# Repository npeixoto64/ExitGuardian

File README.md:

# ExitGuardian
A full product project that watches windows with wireless sensors and has a gateway for the main door with wireless sensors.
When the user opens the exit door to leave, it checks for open windows and doors.

# Documentation
## How to generate the documentation
$ python3 -m venv .venv
$ source .venv/bin/activate
$ pip install -r requirements.txt
$ make html

## Deactivate the python virtual environment
$ deactivate
$ rm -rf .venv

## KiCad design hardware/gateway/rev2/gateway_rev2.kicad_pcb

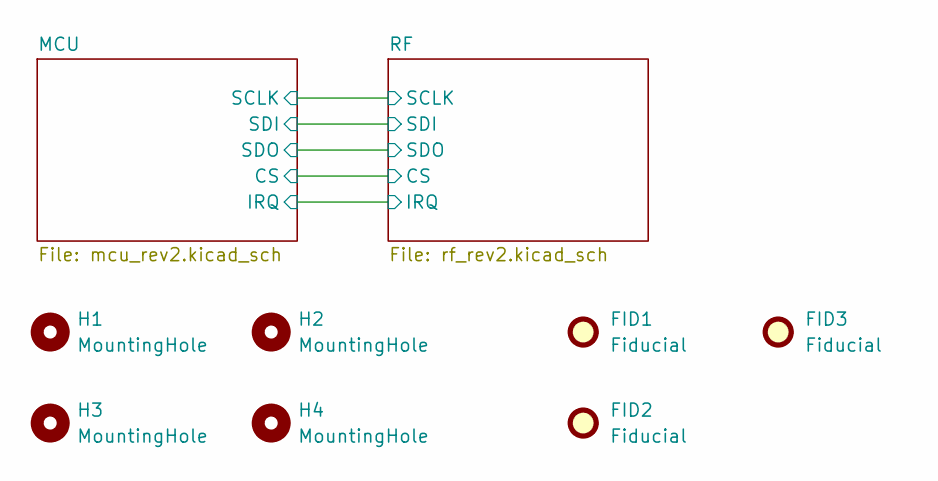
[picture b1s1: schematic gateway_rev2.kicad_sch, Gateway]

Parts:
FID1, FID2, FID3: Fiducial; Fiducial_1mm_Mask2mm
H1, H2, H3, H4: MountingHole; MountingHole_2.5mm

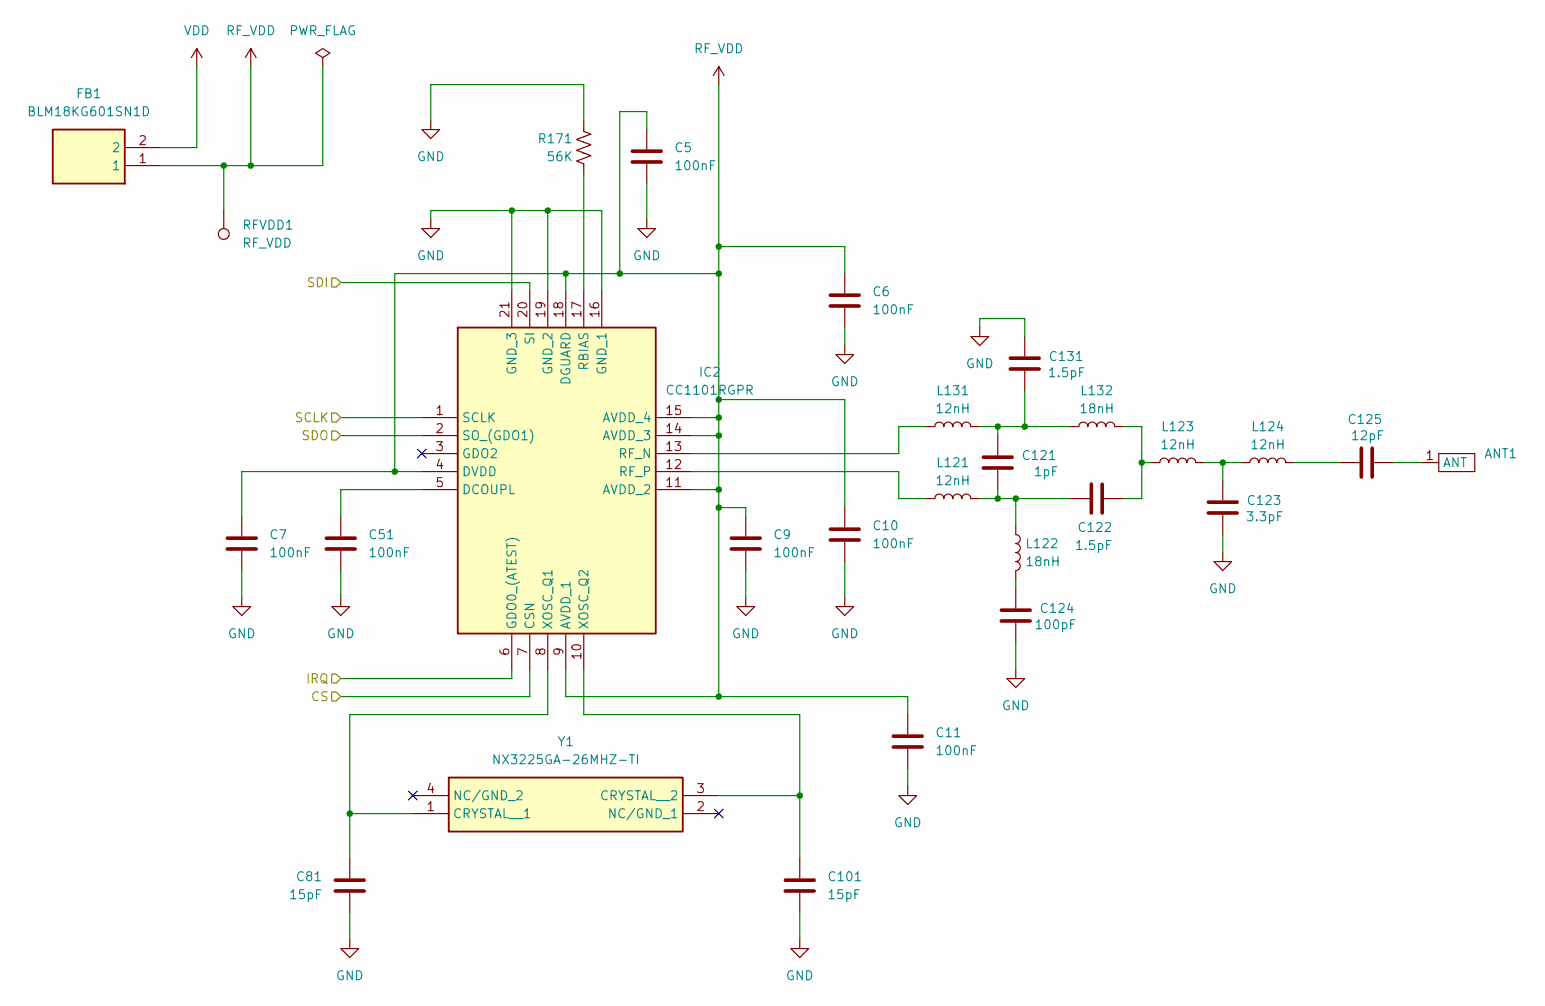
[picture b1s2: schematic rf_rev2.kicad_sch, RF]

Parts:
ANT1: Antenna_hole
C5, C6, C7, C9, C10, C11, C51: 100nF; C_0402_1005Metric; Mouser Part Number 603-CC402KRX7R7BB104
C81, C101: 15pF; C_0402_1005Metric; Mouser Part Number 77-VJ0402D150FXCAJ
C121: 1pF; C_0402_1005Metric; Mouser Part Number 81-GRM1555C1H1R0BA1J
C122, C131: 1.5pF; C_0402_1005Metric; Mouser Part Number 81-GRM1555C1E1R5BA1D
C123: 3.3pF; C_0402_1005Metric; Mouser Part Number 81-GRM1555C1H3R3WA1D
C124: 100pF; C_0402_1005Metric; Mouser Part Number 81-GRM1555C1H101FA1J
C125: 12pF; C_0402_1005Metric; Mouser Part Number 81-GRM1555C1H120FA1D
FB1: BLM18KG601SN1D; BLM18SP221SN1B; Mouser Part Number 81-BLM18KG601SN1D
IC2: CC1101RGPR; QFN50P400X400X100-21N-D; Mouser Part Number 595-CC1101RGPR
L121, L123, L124, L131: 12nH; L_0402_1005Metric; Mouser Part Number 81-LQW15AN12NJ80D
L122, L132: 18nH; L_0402_1005Metric; Mouser Part Number 81-LQG15HH18NJ02D
R171: 56K; R_0402_1005Metric; Mouser Part Number 667-ERJ-PA2F5602X
RFVDD1: RF_VDD; TestPoint_Pad_D1.0mm
Y1: NX3225GA-26MHZ-TI; NX3225GA26000MSTDCRG2; Mouser Part Number 344-NX3225GA26MHZTI

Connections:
/MCU/CS: IC2.7 (CSN); also elsewhere on the board
/MCU/IRQ: IC2.6 (GDO0_(ATEST)); also elsewhere on the board
/MCU/SCLK: IC2.1 (SCLK); also elsewhere on the board
/MCU/SDI: IC2.20 (SI); also elsewhere on the board
/MCU/SDO: IC2.2 (SO_(GDO1)); also elsewhere on the board
GND: C5.2, C6.2, C7.2, C9.2, C10.2, C11.2, C51.2, C81.2, C101.2, C123.1, C124.1, C131.2, IC2.16 (GND_1), IC2.19 (GND_2), IC2.21 (GND_3), R171.2; also elsewhere on the board
unnamed: ANT1.1 (ANT_1), C125.2
unnamed: C121.1, C122.1, L121.2, L122.1
unnamed: C121.2, C131.1, L131.2, L132.1
unnamed: C122.2, L123.1, L132.2
unnamed: C123.2, L123.2, L124.1
unnamed: C124.2, L122.2
unnamed: C125.1, L124.2
unnamed: C51.1, IC2.5 (DCOUPL)
unnamed: IC2.17 (RBIAS), R171.1
unnamed: IC2.13 (RF_N), L131.1
unnamed: IC2.12 (RF_P), L121.1
unnamed: C81.1, IC2.8 (XOSC_Q1), Y1.1 (CRYSTAL__1)
unnamed: C101.1, IC2.10 (XOSC_Q2), Y1.3 (CRYSTAL__2)
RF_VDD: C5.1, C6.1, C7.1, C9.1, C10.1, C11.1, FB1.1, IC2.4 (DVDD), IC2.9 (AVDD_1), IC2.11 (AVDD_2), IC2.14 (AVDD_3), IC2.15 (AVDD_4), IC2.18 (DGUARD), RFVDD1.1 (1_1)
VDD: FB1.2; also elsewhere on the board

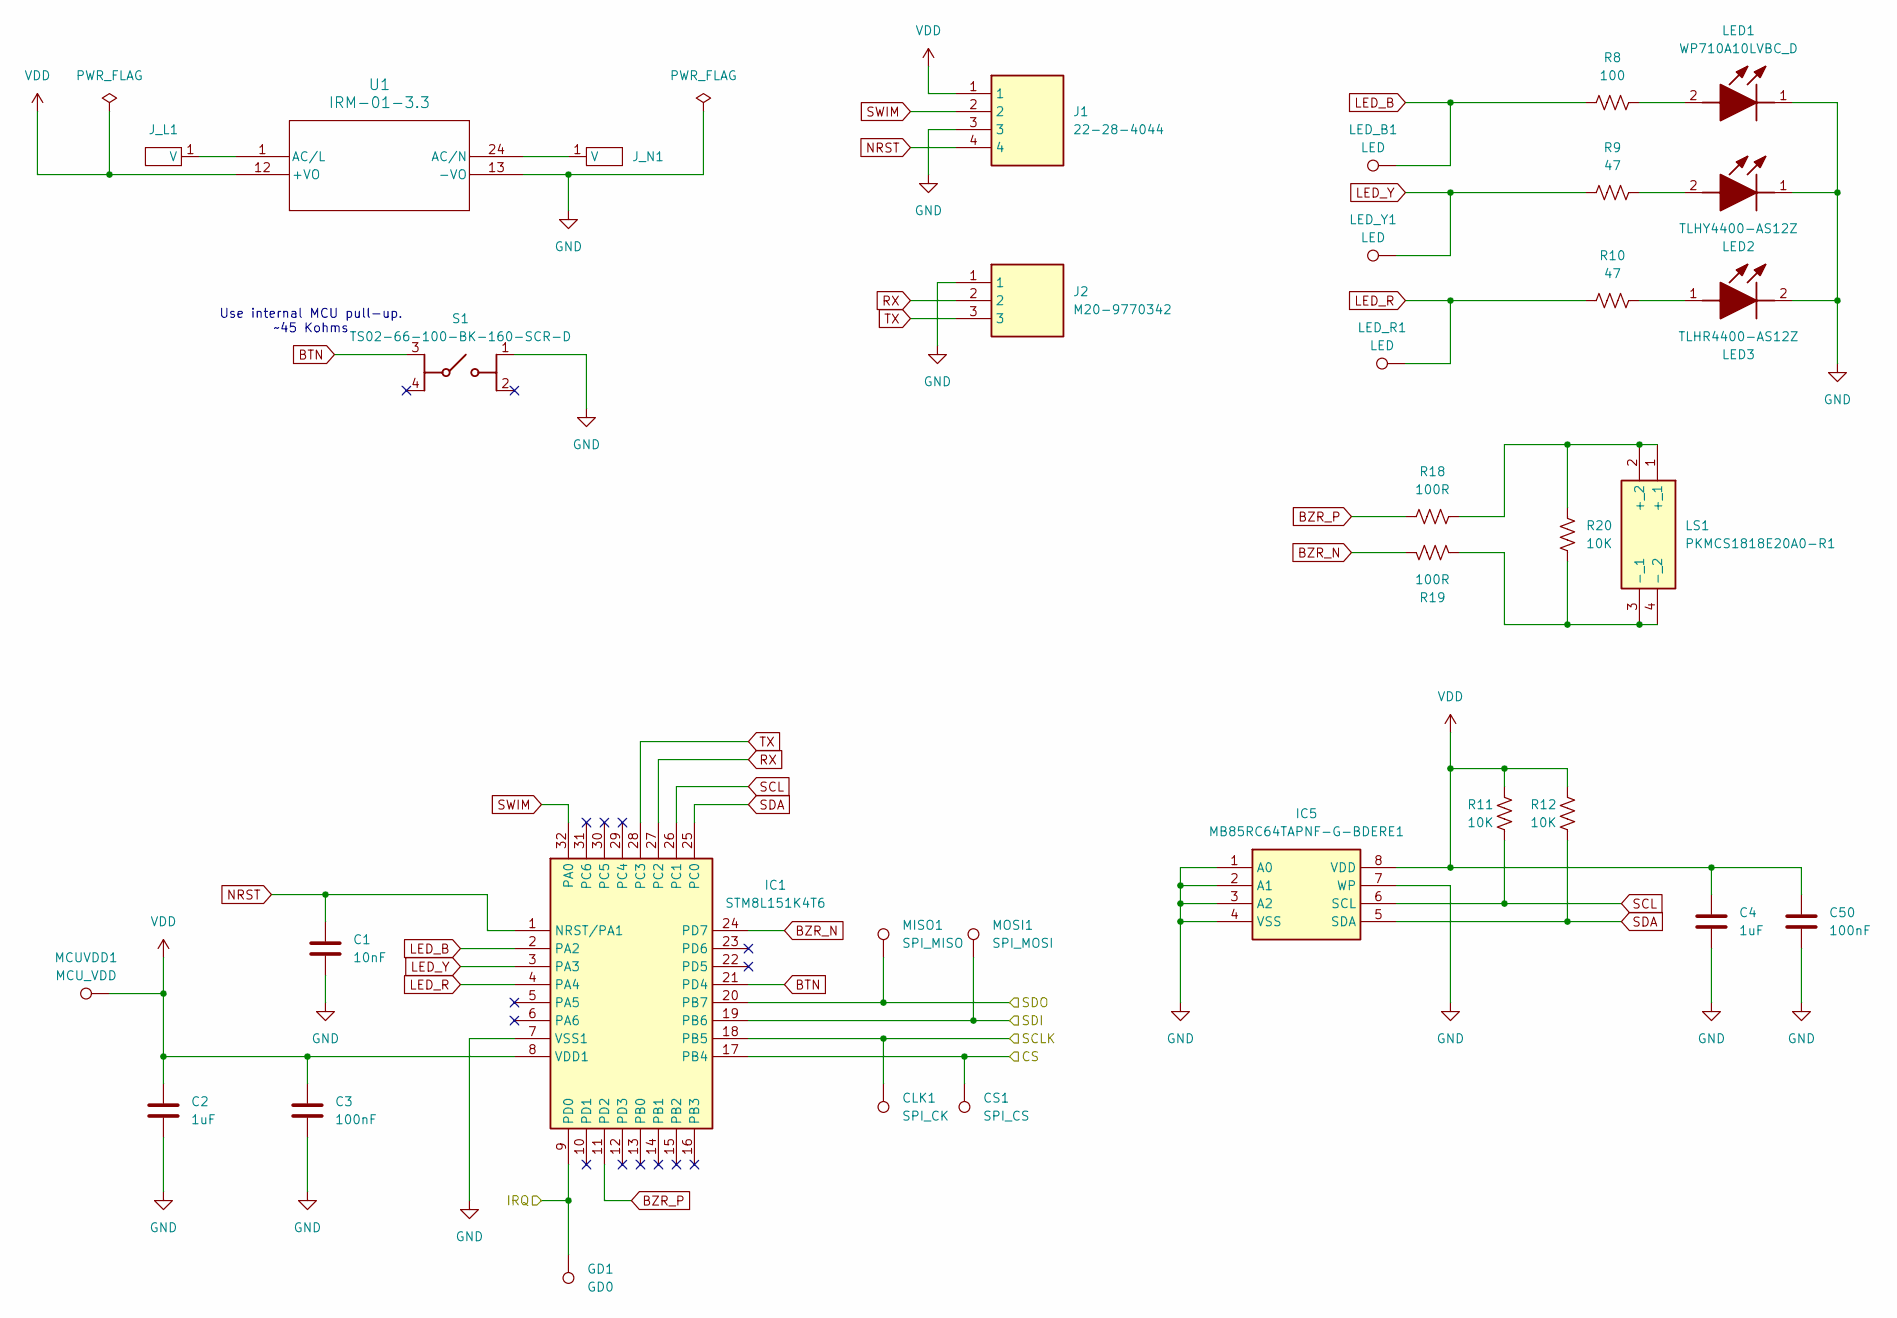
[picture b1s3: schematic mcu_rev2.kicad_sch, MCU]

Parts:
C1: 10nF; C_0402_1005Metric; Mouser Part Number 963-MSAST105SB7103KF
C2, C4: 1uF; C_0402_1005Metric; Mouser Part Number 581-KGM05AV50J105ZH
C3, C50: 100nF; C_0402_1005Metric; Mouser Part Number 603-CC402KRX7R7BB104
CLK1: SPI_CK; TestPoint_Pad_D1.0mm
CS1: SPI_CS; TestPoint_Pad_D1.0mm
GD1: GD0; TestPoint_Pad_D1.0mm
IC1: STM8L151K4T6; QFP80P900X900X160-32N; Mouser Part Number 511-STM8L151K4T6
IC5: MB85RC64TAPNF-G-BDERE1; SOIC127P602X173-8N; Mouser Part Number 249-85C64TAPNFGBDR1
J1: 22-28-4044; HDRV4W66P0X254_1X4_1016X249X1067P; Mouser Part Number 538-22-28-4044
J2: M20-9770342; HDRV3W66P0X254_1X3_762X254X855P; Mouser Part Number 855-M20-9770342
J_L1: 230V
J_N1: 230V
LED1: WP710A10LVBC_D; WP710A10LVBCD; Mouser Part Number 604-WP710A10LVBCD
LED2: TLHY4400-AS12Z; TLHY4400AS12Z; Mouser Part Number 78-TLHY4400-AS12Z
LED3: TLHR4400-AS12Z; TLHR4400AS12Z; Mouser Part Number 78-TLHY4400-AS12Z
LED_B1: LED; TestPoint_Pad_D1.0mm
LED_R1: LED; TestPoint_Pad_D1.0mm
LED_Y1: LED; TestPoint_Pad_D1.0mm
LS1: PKMCS1818E20A0-R1; PKMCS1818E20A0R1; Mouser Part Number 81-PKMCS1818E20A0-R1
MCUVDD1: MCU_VDD; TestPoint_Pad_D1.0mm
MISO1: SPI_MISO; TestPoint_Pad_D1.0mm
MOSI1: SPI_MOSI; TestPoint_Pad_D1.0mm
R8: 100; R_0402_1005Metric; Mouser Part Number 594-MCS04020C1000FE0
R9, R10: 47; R_0402_1005Metric; Mouser Part Number 594-MCS04020C4709FE0
R11, R12, R20: 10K; R_0402_1005Metric; Mouser Part Number 594-MCS04020C1002FE0
R18, R19: 100R; R_0402_1005Metric; Mouser Part Number 594-MCS04020C1000FE0
S1: TS02-66-100-BK-160-SCR-D; TS0266100BK100LCRD; Mouser Part Number 179-TS0266100BK160SC
U1: IRM-01-3.3; IRM-01-3-3; Mouser Part Number 709-IRM01-3.3

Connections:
/MCU/CS: CS1.1 (1_1), IC1.17 (PB4); also elsewhere on the board
/MCU/IRQ: GD1.1 (1_1), IC1.9 (PD0); also elsewhere on the board
/MCU/SCLK: CLK1.1 (1_1), IC1.18 (PB5); also elsewhere on the board
/MCU/SDI: IC1.19 (PB6), MOSI1.1 (1_1); also elsewhere on the board
/MCU/SDO: IC1.20 (PB7), MISO1.1 (1_1); also elsewhere on the board
BTN: IC1.21 (PD4), S1.3 (COM_1)
BZR_N: IC1.24 (PD7), R19.2
BZR_P: IC1.11 (PD2), R18.2
GND: C1.2, C2.2, C3.2, C4.2, C50.2, IC1.7 (VSS1), IC5.1 (A0), IC5.2 (A1), IC5.3 (A2), IC5.4 (VSS), IC5.7 (WP), J1.3, J2.1, LED1.1 (K), LED2.1 (K), LED3.2 (K), S1.1 (NO_1), U1.13 (-VO); also elsewhere on the board
LED_B: IC1.2 (PA2), LED_B1.1 (1_1), R8.1
LED_R: IC1.4 (PA4), LED_R1.1 (1_1), R10.1
LED_Y: IC1.3 (PA3), LED_Y1.1 (1_1), R9.1
NRST: C1.1, IC1.1 (NRST/PA1), J1.4
unnamed: J_L1.1 (V_1), U1.1 (AC/L)
unnamed: J_N1.1 (V_1), U1.24 (AC/N)
unnamed: LED1.2 (A), R8.2
unnamed: LED2.2 (A), R9.2
unnamed: LED3.1 (A), R10.2
unnamed: LS1.1 (+_1), LS1.2 (+_2), R18.1, R20.2
unnamed: LS1.3 (-_1), LS1.4 (-_2), R19.1, R20.1
RX: IC1.27 (PC2), J2.2
SCL: IC1.26 (PC1), IC5.6 (SCL), R11.1
SDA: IC1.25 (PC0), IC5.5 (SDA), R12.1
SWIM: IC1.32 (PA0), J1.2
TX: IC1.28 (PC3), J2.3
VDD: C2.1, C3.1, C4.1, C50.1, IC1.8 (VDD1), IC5.8 (VDD), J1.1, MCUVDD1.1 (1_1), R11.2, R12.2, U1.12 (+VO); also elsewhere on the board

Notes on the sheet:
Use internal MCU pull-up. ~45 Kohms

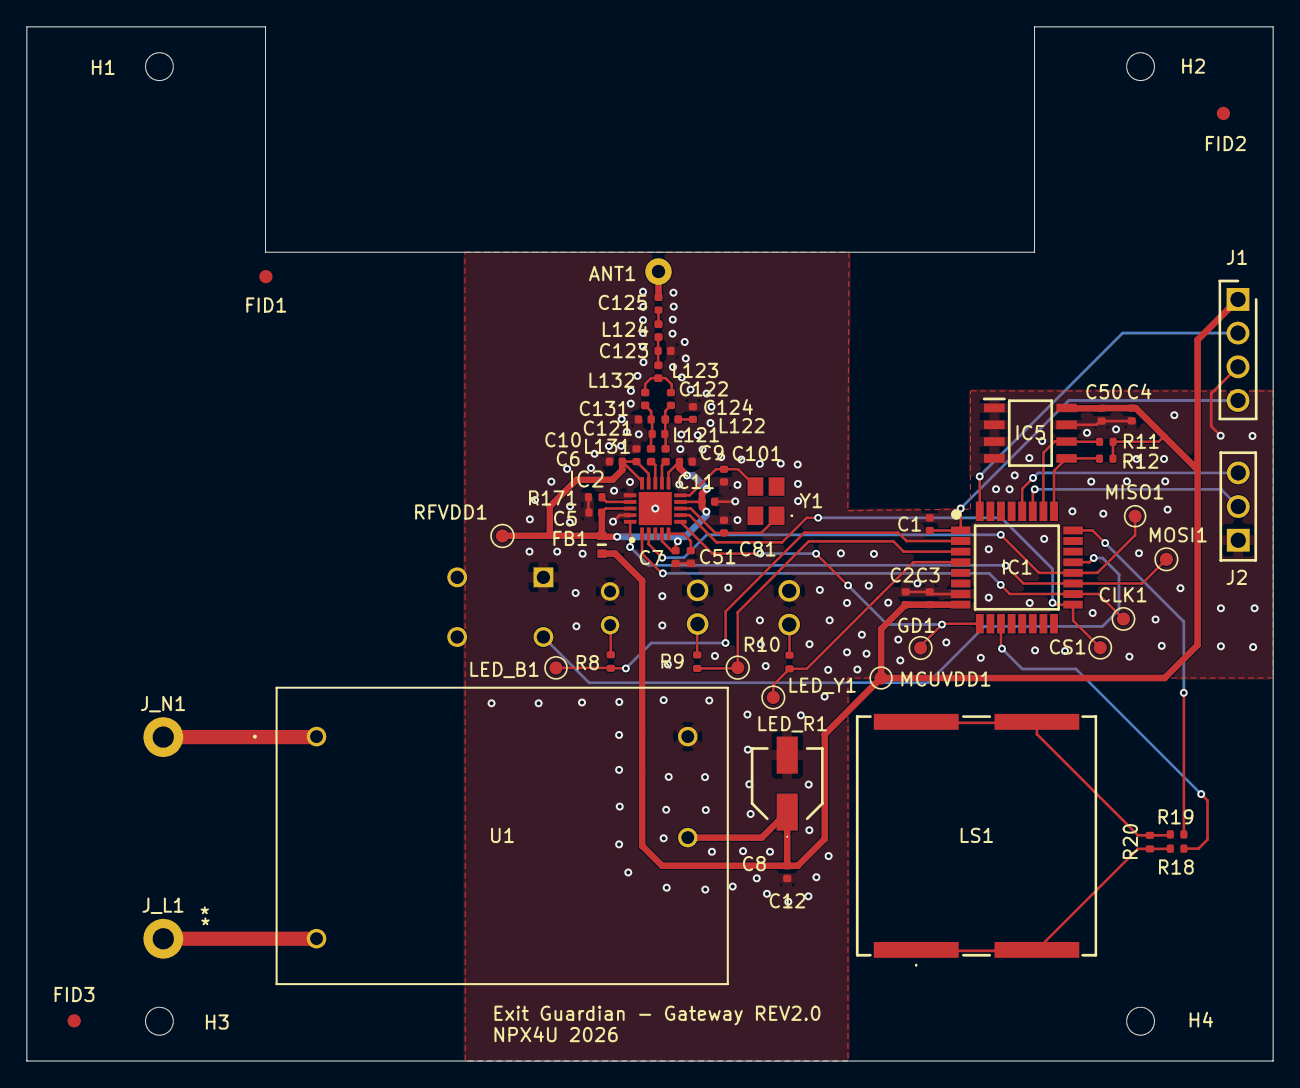
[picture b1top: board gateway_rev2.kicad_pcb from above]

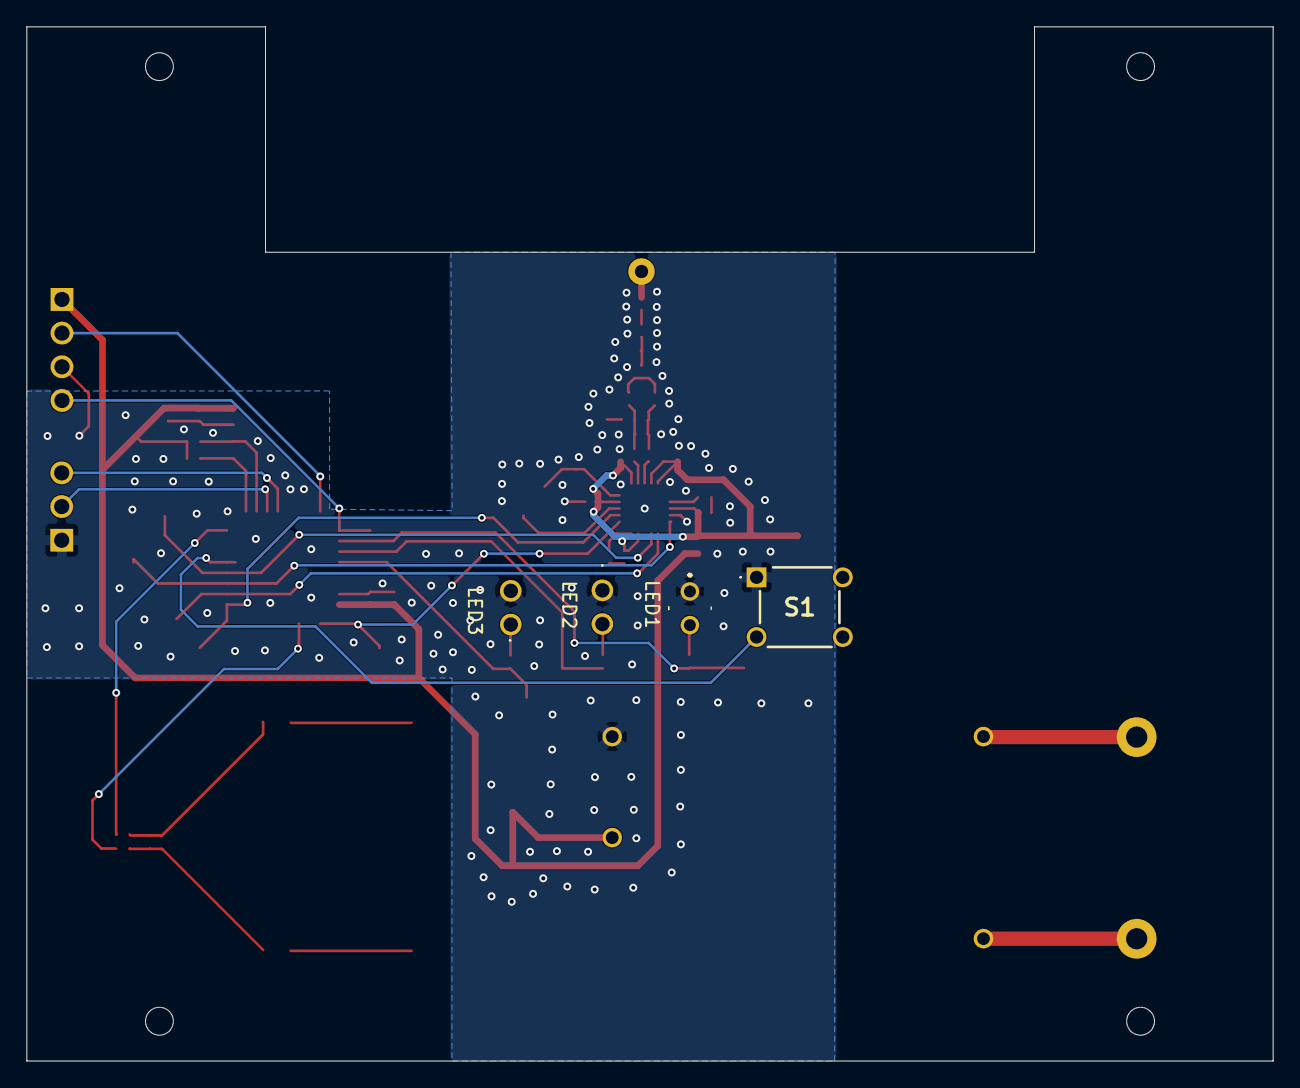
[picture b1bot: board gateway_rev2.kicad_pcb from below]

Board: 2 copper layers, 94.0 x 78.0 mm, 70 parts (4 on the bottom side), 40 nets.

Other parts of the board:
C8: 47uF; EEE0GA101SR
C12: 100nF; C_0402_1005Metric

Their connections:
GND: C8.2 (-), C12.2; also elsewhere on the board
VDD: C8.1 (+), C12.1; also elsewhere on the board

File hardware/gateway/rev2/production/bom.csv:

Designator,Footprint,Quantity,Value,LCSC Part #
C1,0402,1,10nF,
"C10, C11, C12, C3, C5, C50, C51, C6, C7, C9",0402,10,100nF,
"C101, C81",0402,2,15pF,
C121,0402,1,1pF,
"C122, C131",0402,2,1.5pF,
C123,0402,1,3.3pF,
C124,0402,1,100pF,
C125,0402,1,12pF,
"C2, C4",0402,2,1uF,
C8,EEE0GA101SR,1,47uF,
FB1,BLM18SP221SN1B,1,BLM18KG601SN1D,
IC1,QFP80P900X900X160-32N,1,STM8L151K4T6,
IC2,QFN50P400X400X100-21N-D,1,CC1101RGPR,
IC5,SOIC127P602X173-8N,1,MB85RC64TAPNF-G-BDERE1,
"L121, L123, L124, L131",0402,4,12nH,
"L122, L132",0402,2,18nH,
LS1,PKMCS1818E20A0R1,1,PKMCS1818E20A0-R1,
"R10, R9",0402,2,47,
"R11, R12, R20",0402,3,10K,
R171,0402,1,56K,
"R18, R19",0402,2,100R,
R8,0402,1,100,
U1,IRM-01-3-3,1,IRM-01-3.3,
Y1,NX3225GA26000MSTDCRG2,1,NX3225GA-26MHZ-TI,

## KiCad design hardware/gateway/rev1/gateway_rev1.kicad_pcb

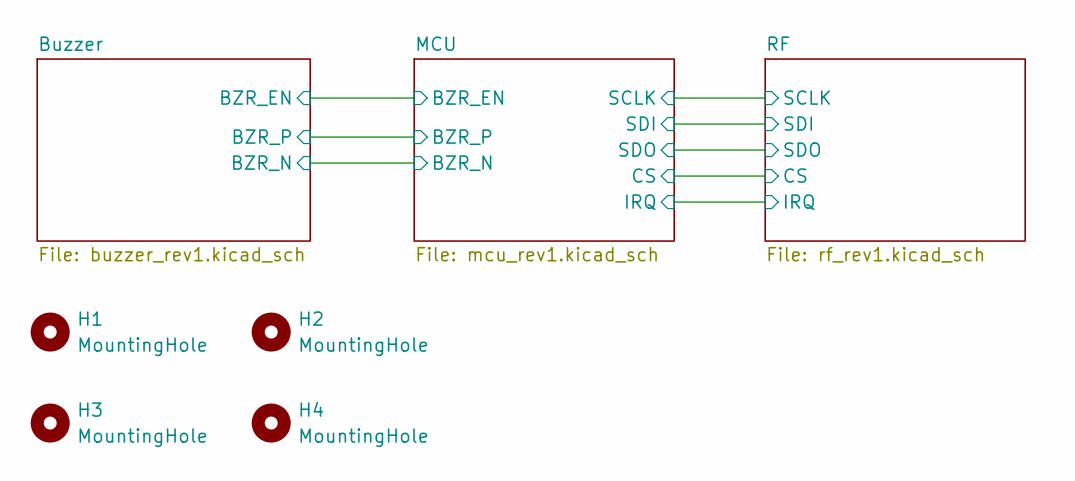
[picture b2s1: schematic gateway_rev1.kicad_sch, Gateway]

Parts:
H1, H2, H3, H4: MountingHole; MountingHole_2.5mm

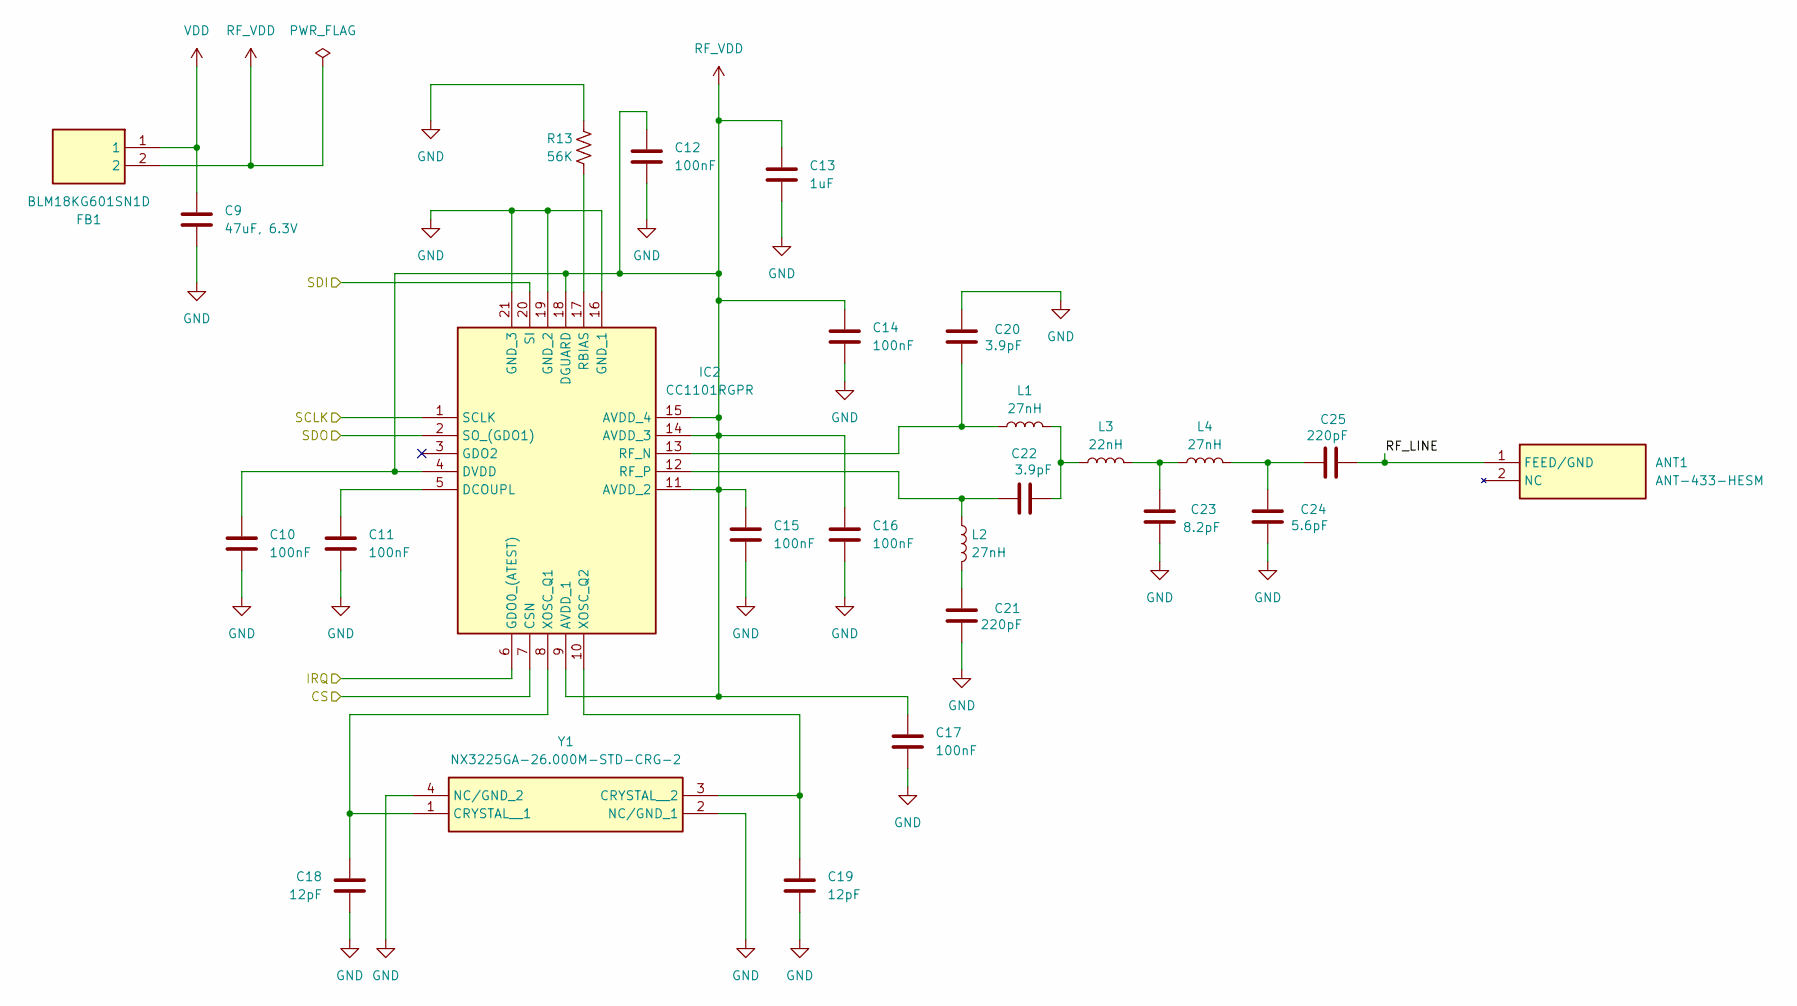
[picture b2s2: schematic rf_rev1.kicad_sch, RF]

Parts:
ANT1: ANT-433-HESM; ANT433HESM; Mouser Part Number 712-ANT-433-HESM
C9: 47uF, 6.3V; C_1206_3216Metric; Mouser Part Number 963-JMK325B7476MM-PR
C10, C11, C12, C14, C15, C16, C17: 100nF; C_0402_1005Metric; Mouser Part Number 603-CC402KRX7R7BB104
C13: 1uF; C_0402_1005Metric; Mouser Part Number 81-GXT155R60J105KE1D
C18, C19: 12pF; C_0402_1005Metric; Mouser Part Number 81-GRM1555C1H120FA1D
C20, C22: 3.9pF; C_0402_1005Metric; Mouser Part Number 81-GRM1555C1E3R9CA1D
C21, C25: 220pF; C_0402_1005Metric; Mouser Part Number 81-GRM0225C1C221JA2L
C23: 8.2pF; C_0402_1005Metric; Mouser Part Number 81-GCQ0335C1H8R2WB1D
C24: 5.6pF; C_0402_1005Metric; Mouser Part Number 81-GCQ0335C1H5R6BB1D
FB1: BLM18KG601SN1D; BLM18SP221SN1B; Mouser Part Number 81-BLM18KG601SN1D
IC2: CC1101RGPR; QFN50P400X400X100-21N-D; Mouser Part Number 595-CC1101RGPR
L1, L2, L4: 27nH; L_0402_1005Metric; Mouser Part Number 81-LQG15HS27NJ02D
L3: 22nH; L_0402_1005Metric; Mouser Part Number 81-LQW15CA22NJ00D
R13: 56K; R_0402_1005Metric; Mouser Part Number 667-ERJ-PA2F5602X
Y1: NX3225GA-26.000M-STD-CRG-2; NX3225GA26000MSTDCRG2; Mouser Part Number 344-NX3225GA26MSTRG2

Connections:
/MCU/CS: IC2.7 (CSN); also elsewhere on the board
/MCU/IRQ: IC2.6 (GDO0_(ATEST)); also elsewhere on the board
/MCU/SCLK: IC2.1 (SCLK); also elsewhere on the board
/MCU/SDI: IC2.20 (SI); also elsewhere on the board
/MCU/SDO: IC2.2 (SO_(GDO1)); also elsewhere on the board
/RF/RF_LINE: ANT1.1 (FEED/GND), C25.2
GND: C9.2, C10.2, C11.2, C12.2, C13.2, C14.2, C15.2, C16.2, C17.2, C18.2, C19.2, C20.2, C21.1, C23.1, C24.1, IC2.16 (GND_1), IC2.19 (GND_2), IC2.21 (GND_3), R13.2, Y1.2 (NC/GND_1), Y1.4 (NC/GND_2); also elsewhere on the board
unnamed: C21.2, L2.2
unnamed: C22.1, L1.2, L3.1
unnamed: C23.2, L3.2, L4.1
unnamed: C24.2, C25.1, L4.2
unnamed: C11.1, IC2.5 (DCOUPL)
unnamed: IC2.17 (RBIAS), R13.1
unnamed: C20.1, IC2.13 (RF_N), L1.1
unnamed: C22.2, IC2.12 (RF_P), L2.1
unnamed: C18.1, IC2.8 (XOSC_Q1), Y1.1 (CRYSTAL__1)
unnamed: C19.1, IC2.10 (XOSC_Q2), Y1.3 (CRYSTAL__2)
RF_VDD: C10.1, C12.1, C13.1, C14.1, C15.1, C16.1, C17.1, FB1.2, IC2.4 (DVDD), IC2.9 (AVDD_1), IC2.11 (AVDD_2), IC2.14 (AVDD_3), IC2.15 (AVDD_4), IC2.18 (DGUARD)
VDD: C9.1, FB1.1; also elsewhere on the board

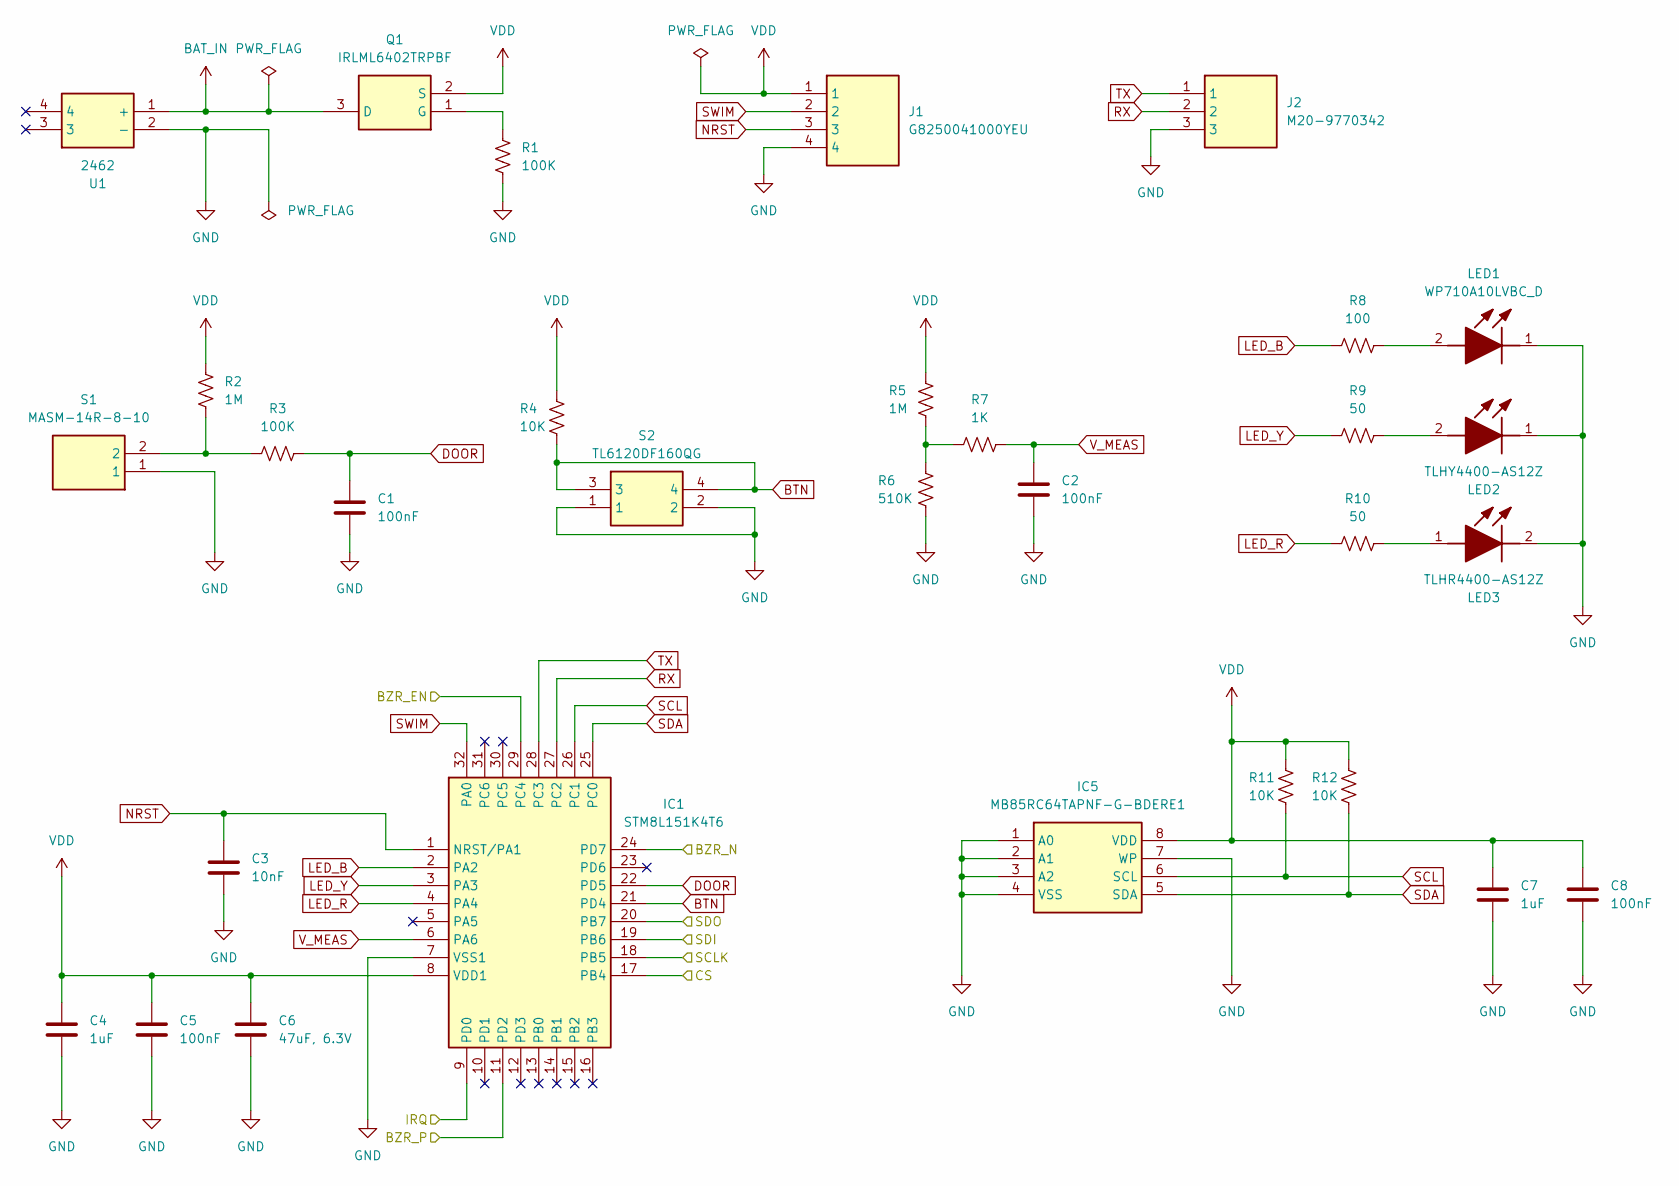
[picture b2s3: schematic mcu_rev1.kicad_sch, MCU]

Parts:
C1, C2, C5, C8: 100nF; C_0402_1005Metric; Mouser Part Number 603-CC402KRX7R7BB104
C3: 10nF; C_0402_1005Metric; Mouser Part Number 81-GXT155R71C103KE1D
C4, C7: 1uF; C_0402_1005Metric; Mouser Part Number 81-GXT155R60J105KE1D
C6: 47uF, 6.3V; C_1206_3216Metric; Mouser Part Number 963-JMK325B7476MM-PR
IC1: STM8L151K4T6; QFP80P900X900X160-32N; Mouser Part Number 511-STM8L151K4T6
IC5: MB85RC64TAPNF-G-BDERE1; SOIC127P602X173-8N; Mouser Part Number 249-85C64TAPNFGBDR1
J1: G8250041000YEU; HDRV4W55P0X200_1X4_800X200X635P; Mouser Part Number 523-G8250041000YEU
J2: M20-9770342; HDRV3W66P0X254_1X3_762X254X855P; Mouser Part Number 855-M20-9770342
LED1: WP710A10LVBC_D; WP710A10LVBCD; Mouser Part Number 604-WP710A10LVBCD
LED2: TLHY4400-AS12Z; TLHY4400AS12Z; Mouser Part Number 78-TLHY4400-AS12Z
LED3: TLHR4400-AS12Z; TLHR4400AS12Z; Mouser Part Number 78-TLHR4400-AS12Z
Q1: IRLML6402TRPBF; SOT95P237X112-3N; Mouser Part Number 942-IRLML6402TRPBF
R1, R3: 100K; R_0402_1005Metric; Mouser Part Number 603-RC0402JR-7D100KL
R2, R5: 1M; R_0402_1005Metric; Mouser Part Number 667-ERJ-2RKD1004X
R4, R11, R12: 10K; R_0402_1005Metric; Mouser Part Number 603-AC0402JR-7D10KL
R6: 510K; R_0402_1005Metric; Mouser Part Number 667-ERJ-2RKD5103X
R7: 1K; R_0402_1005Metric; Mouser Part Number 603-RC0402JR-7D1KL
R8: 100; R_0402_1005Metric; Mouser Part Number 603-AC0402JR-7D100RL
R9, R10: 50; R_0402_1005Metric; Mouser Part Number 603-AC0402JR-0750RL
S1: MASM-14R-8-10; MASM14R810; Mouser Part Number 934-MASM-14R-8-10
S2: TL6120DF160QG; Mouser Part Number 612-TL6120DF160QG
U1: 2462; Mouser Part Number 534-2462

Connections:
/Buzzer/BZR_EN: IC1.29 (PC4); also elsewhere on the board
/Buzzer/BZR_N: IC1.24 (PD7); also elsewhere on the board
/Buzzer/BZR_P: IC1.11 (PD2); also elsewhere on the board
/MCU/CS: IC1.17 (PB4); also elsewhere on the board
/MCU/IRQ: IC1.9 (PD0); also elsewhere on the board
/MCU/SCLK: IC1.18 (PB5); also elsewhere on the board
/MCU/SDI: IC1.19 (PB6); also elsewhere on the board
/MCU/SDO: IC1.20 (PB7); also elsewhere on the board
BAT_IN: Q1.3 (D), U1.1 (+)
BTN: IC1.21 (PD4), R4.1, S2.3, S2.4
DOOR: C1.1, IC1.22 (PD5), R3.2
GND: C1.2, C2.2, C3.2, C4.2, C5.2, C6.2, C7.2, C8.2, IC1.7 (VSS1), IC5.1 (A0), IC5.2 (A1), IC5.3 (A2), IC5.4 (VSS), IC5.7 (WP), J1.4, J2.3, LED1.1 (K), LED2.1 (K), LED3.2 (K), R1.2, R6.1, S1.1, S2.1, S2.2, U1.2 (-); also elsewhere on the board
LED_B: IC1.2 (PA2), R8.1
LED_R: IC1.4 (PA4), R10.1
LED_Y: IC1.3 (PA3), R9.1
NRST: C3.1, IC1.1 (NRST/PA1), J1.3
unnamed: LED1.2 (A), R8.2
unnamed: LED2.2 (A), R9.2
unnamed: LED3.1 (A), R10.2
unnamed: Q1.1 (G), R1.1
unnamed: R2.1, R3.1, S1.2
unnamed: R5.1, R6.2, R7.1
RX: IC1.27 (PC2), J2.2
SCL: IC1.26 (PC1), IC5.6 (SCL), R11.1
SDA: IC1.25 (PC0), IC5.5 (SDA), R12.1
SWIM: IC1.32 (PA0), J1.2
TX: IC1.28 (PC3), J2.1
VDD: C4.1, C5.1, C6.1, C7.1, C8.1, IC1.8 (VDD1), IC5.8 (VDD), J1.1, Q1.2 (S), R2.2, R4.2, R5.2, R11.2, R12.2; also elsewhere on the board
V_MEAS: C2.1, IC1.6 (PA6), R7.2

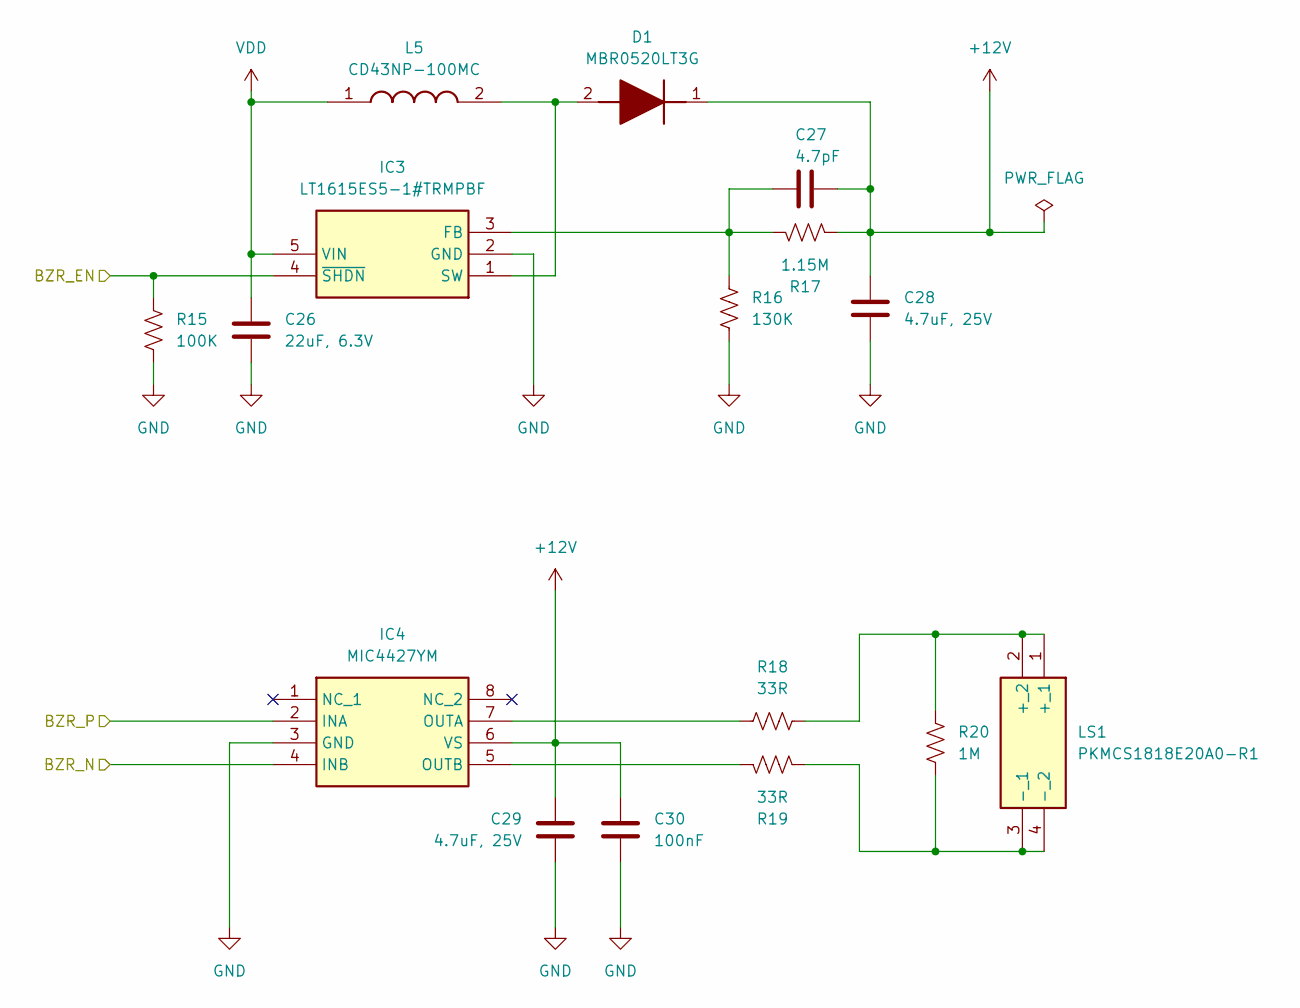
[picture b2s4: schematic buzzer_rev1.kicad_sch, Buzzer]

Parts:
C26: 22uF, 6.3V; C_1206_3216Metric; Mouser Part Number 81-GGM31CD70J226KE2L
C27: 4.7pF; C_0402_1005Metric; Mouser Part Number 81-GCM1555C2A4R7BE2D
C28, C29: 4.7uF, 25V; C_0805_2012Metric; Mouser Part Number 963-MCAST21GBC7475KT
C30: 100nF; C_0402_1005Metric; Mouser Part Number 603-CC402KRX7R7BB104
D1: MBR0520LT3G; SOD3716X135N; Mouser Part Number 863-MBR0520LT3G
IC3: LT1615ES5-1#TRMPBF; SOT95P280X100-5N; Mouser Part Number 584-1615ES5-1TRMPBF
IC4: MIC4427YM; SOIC127P599X173-8N; Mouser Part Number 998-MIC4427YM
L5: CD43NP-100MC; CD43NP100MC; Mouser Part Number 851-CD43NP-100MC
LS1: PKMCS1818E20A0-R1; PKMCS1818E20A0R1; Mouser Part Number 81-PKMCS1818E20A0-R1
R15: 100K; R_0603_1608Metric; Mouser Part Number 594-MCT06030C1003FP5
R16: 130K; R_0402_1005Metric; Mouser Part Number 603-RC0402DR-07130KL
R17: 1.15M; R_0402_1005Metric; Mouser Part Number 603-RC0402FR-071M15L
R18, R19: 33R; R_0603_1608Metric; Mouser Part Number 603-SR0603JR-7T33RL
R20: 1M; R_0603_1608Metric; Mouser Part Number 603-AR0603FR-071ML

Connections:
+12V: C27.1, C28.1, C29.1, C30.1, D1.1 (K), IC4.6 (VS), R17.2
/Buzzer/BZR_EN: IC3.4 (~SHDN), R15.2; also elsewhere on the board
/Buzzer/BZR_N: IC4.4 (INB); also elsewhere on the board
/Buzzer/BZR_P: IC4.2 (INA); also elsewhere on the board
GND: C26.2, C28.2, C29.2, C30.2, IC3.2 (GND), IC4.3 (GND), R15.1, R16.1; also elsewhere on the board
unnamed: D1.2 (A), IC3.1 (SW), L5.2
unnamed: C27.2, IC3.3 (FB), R16.2, R17.1
unnamed: IC4.7 (OUTA), R18.2
unnamed: IC4.5 (OUTB), R19.2
unnamed: LS1.1 (+_1), LS1.2 (+_2), R18.1, R20.2
unnamed: LS1.3 (-_1), LS1.4 (-_2), R19.1, R20.1
VDD: C26.1, IC3.5 (VIN), L5.1; also elsewhere on the board
